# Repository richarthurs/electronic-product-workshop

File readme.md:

## Electronic Product Workshop

This workshop and video series teaches the basics of KiCAD schematic capture and PCB layout, as well as how to create the required documentation to develop electronic products and projects smoothly.

This series is targeted at skilled hobbyists, engineering students, or those involved in a university-level design team.

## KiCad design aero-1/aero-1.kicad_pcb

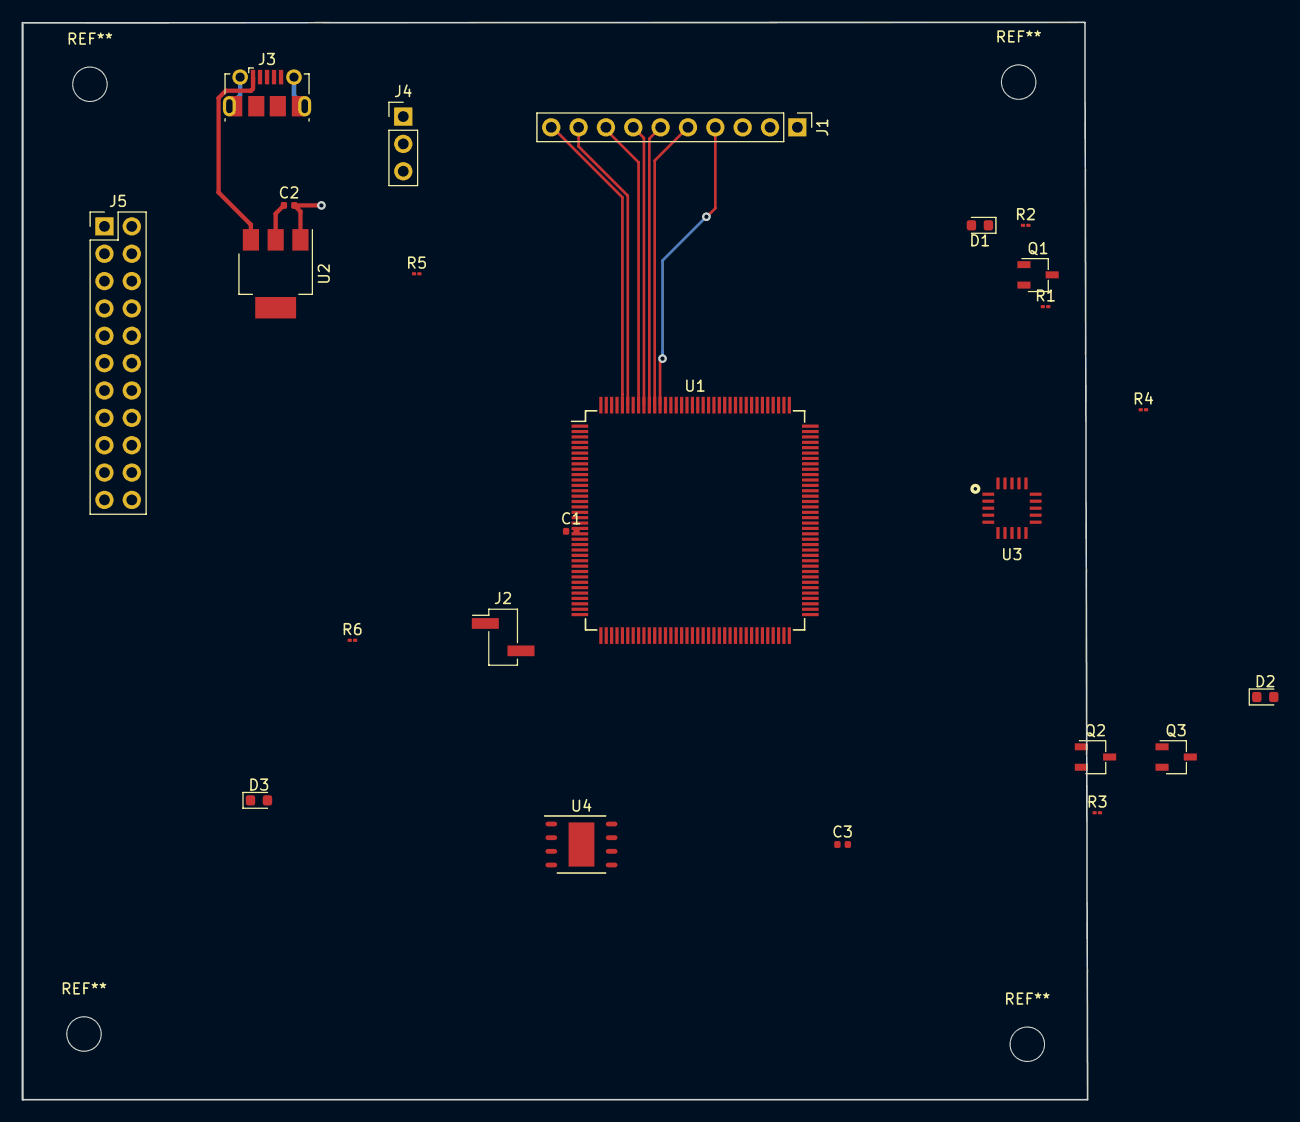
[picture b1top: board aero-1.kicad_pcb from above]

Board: 4 copper layers, 98.9 x 100.0 mm, 24 parts (0 on the bottom side), 36 nets.

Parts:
C1: 1 uF; C_0402_1005Metric
C2: 1uF; C_0402_1005Metric
C3: C_Small; C_0402_1005Metric
D1, D2, D3: LED; LED_0603_1608Metric
J1: Conn_01x10; PinHeader_1x10_P2.54mm_Vertical
J2: Conn_01x02; PinHeader_1x02_P2.54mm_Vertical_SMD_Pin1Left
J3: USB_B_Micro; USB_Micro-B_Molex-105017-0001
J4: Conn_01x03; PinHeader_1x03_P2.54mm_Vertical
J5: Conn_02x11_Odd_Even; PinHeader_2x11_P2.54mm_Vertical
Q1, Q2, Q3: IRF6655; TSOT-23
R1, R3: 10k; C_01005_0402Metric
R2, R4, R6: 270; C_01005_0402Metric
R5: 1M; C_01005_0402Metric
U1: STM32F722ZCTx; LQFP-144_20x20mm_P0.5mm
U2: AZ1117-3.3; SOT-223
U3: AS7262
U4: M25PX32-VMP; DFN-S-8-1EP_6x5mm_P1.27mm

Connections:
3v3_reg: C2.1, J4.1, U2.2
+3V3: C3.1, D1.2, D2.2, D3.2, J4.2, J5.5, J5.6, Q3.2, U3.14, U3.17, U4.8
/Backplane/I2C_SCL: J5.10, U1.42, U3.11
/Backplane/I2C_SDA: J5.8, U1.41, U3.12
BP_1: J5.7, U1.10
BP_2: J5.9, U1.11
BP_3: J5.11, U1.12
BP_4: J5.13, U1.13
DBG_1: Q1.2, R1.1, U1.126
DBG_2: Q2.2, R3.1, U1.127
DQ1: U1.45, U4.2
GND: C1.2, C2.2, C3.2, J2.2, J3.5, J5.21, J5.22, Q1.3, Q2.3, Q3.3, R1.2, R3.2, R5.2, U2.1, U3.16, U4.4, U4.9
unnamed: C1.1, J3.6, R5.1
unnamed: D1.1, R2.1
unnamed: D2.1, R4.1
unnamed: D3.1, R6.1
unnamed: J1.1, U1.46
unnamed: J1.2, U1.47
unnamed: J1.3, U1.48
unnamed: J1.4, U1.133
unnamed: J1.5, U1.134
unnamed: J1.6, U1.135
unnamed: J1.7, U1.136
unnamed: J1.8, U1.137
unnamed: J1.9, U1.139
unnamed: J1.10, U1.140
unnamed: J2.1, J4.3
unnamed: J3.1, U2.3
unnamed: Q1.1, R2.2
unnamed: Q2.1, R4.2
unnamed: Q3.1, R6.2
unnamed: U1.26, U4.5
unnamed: U1.27, U4.6
unnamed: U1.28, U4.1
unnamed: U1.29, U4.3
unnamed: U1.44, U4.7

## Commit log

2019-12-31 Add workshop slides
2019-12-31 Add kicad files
